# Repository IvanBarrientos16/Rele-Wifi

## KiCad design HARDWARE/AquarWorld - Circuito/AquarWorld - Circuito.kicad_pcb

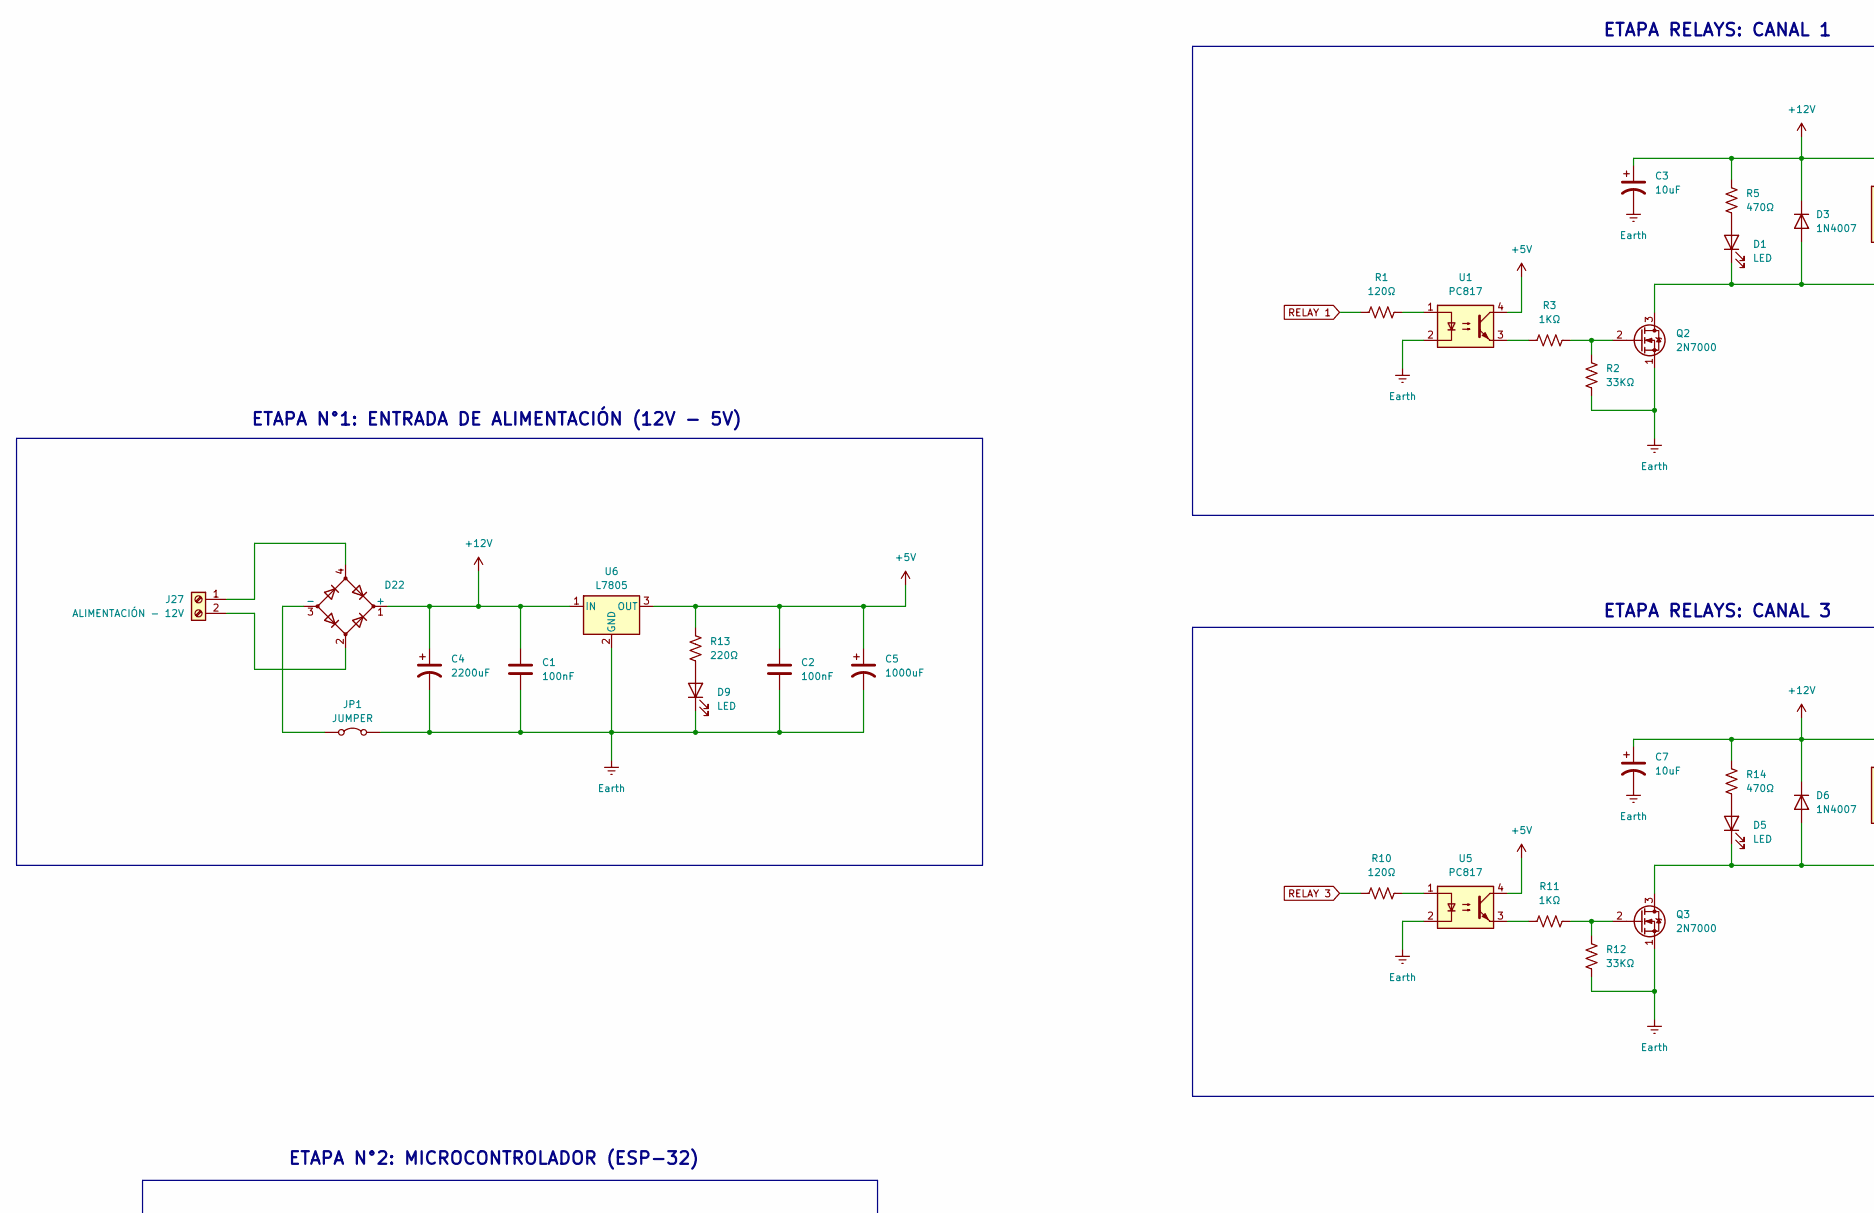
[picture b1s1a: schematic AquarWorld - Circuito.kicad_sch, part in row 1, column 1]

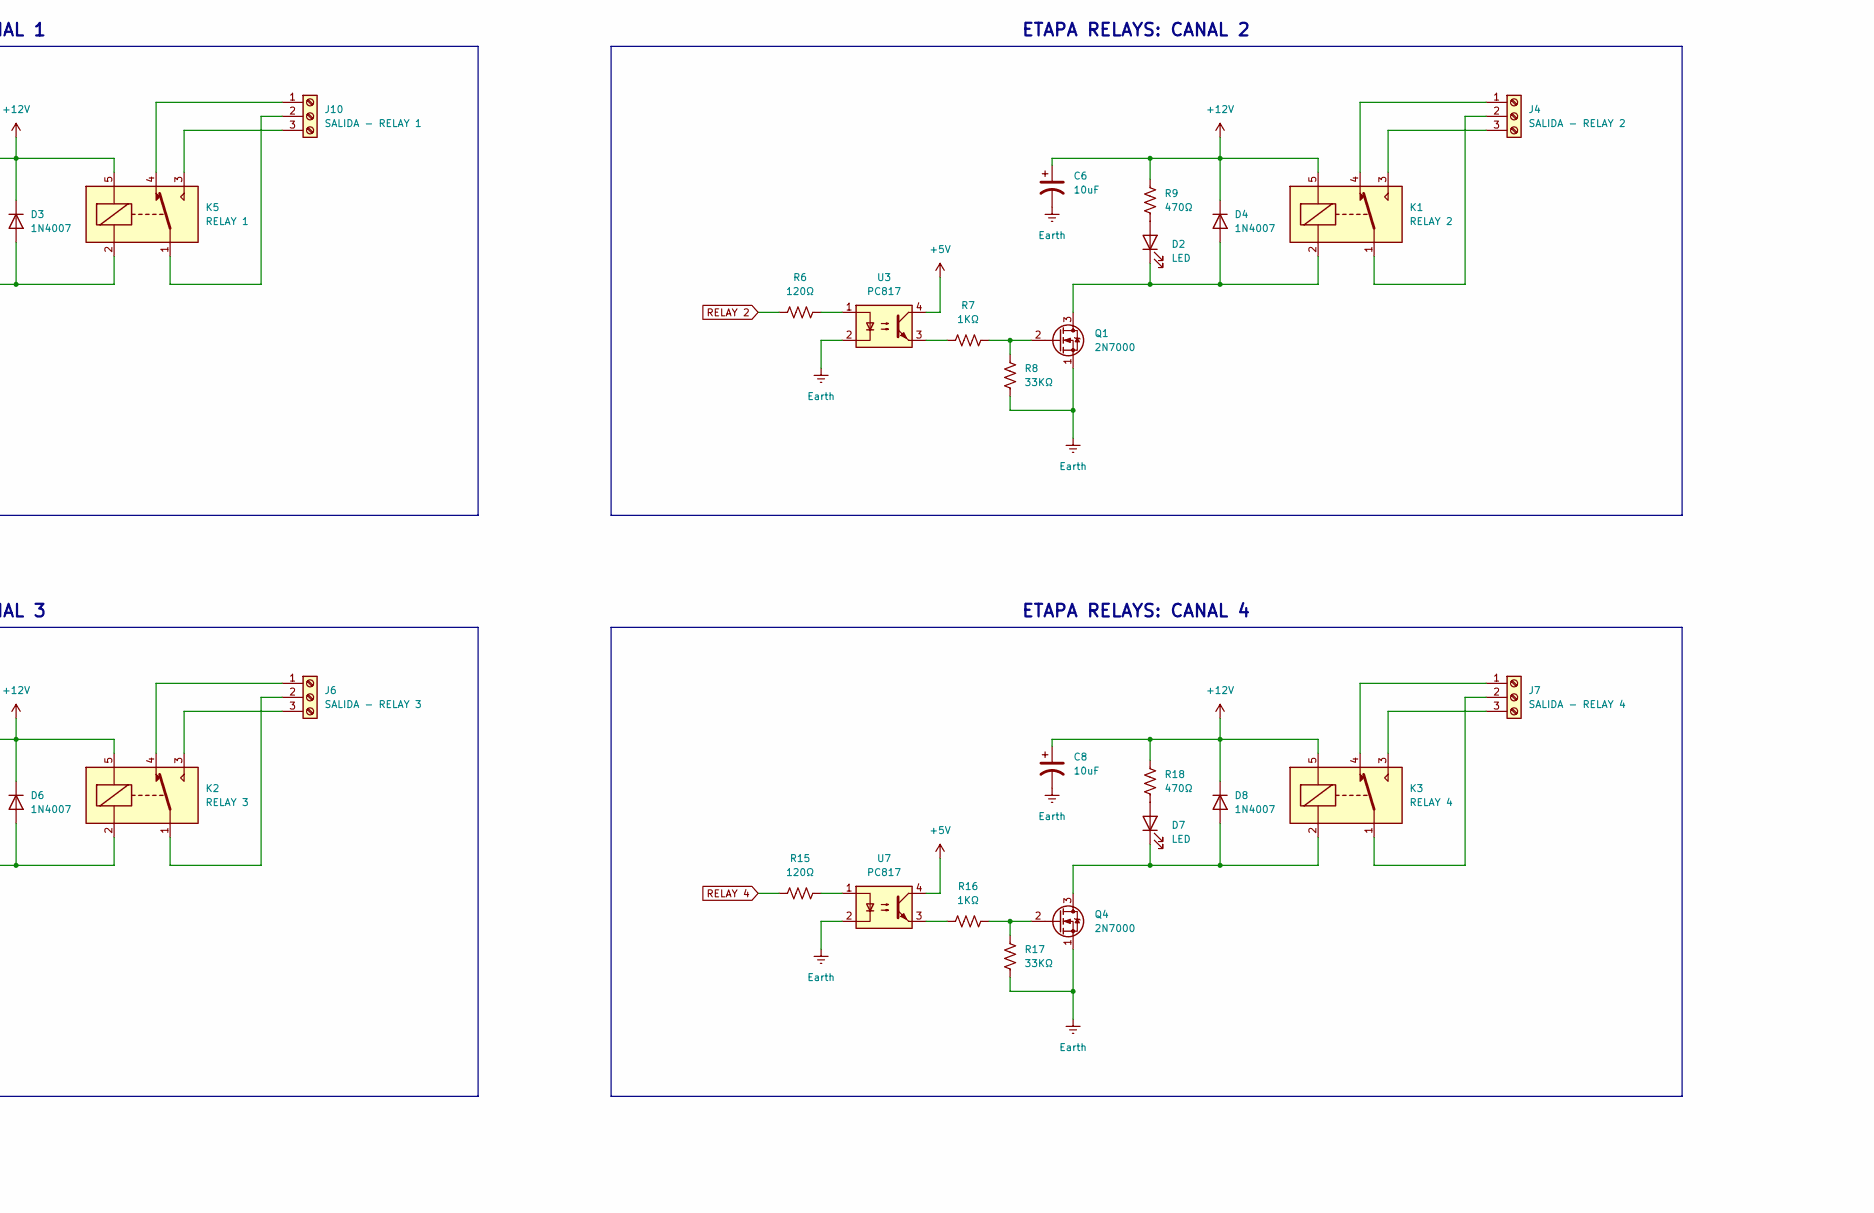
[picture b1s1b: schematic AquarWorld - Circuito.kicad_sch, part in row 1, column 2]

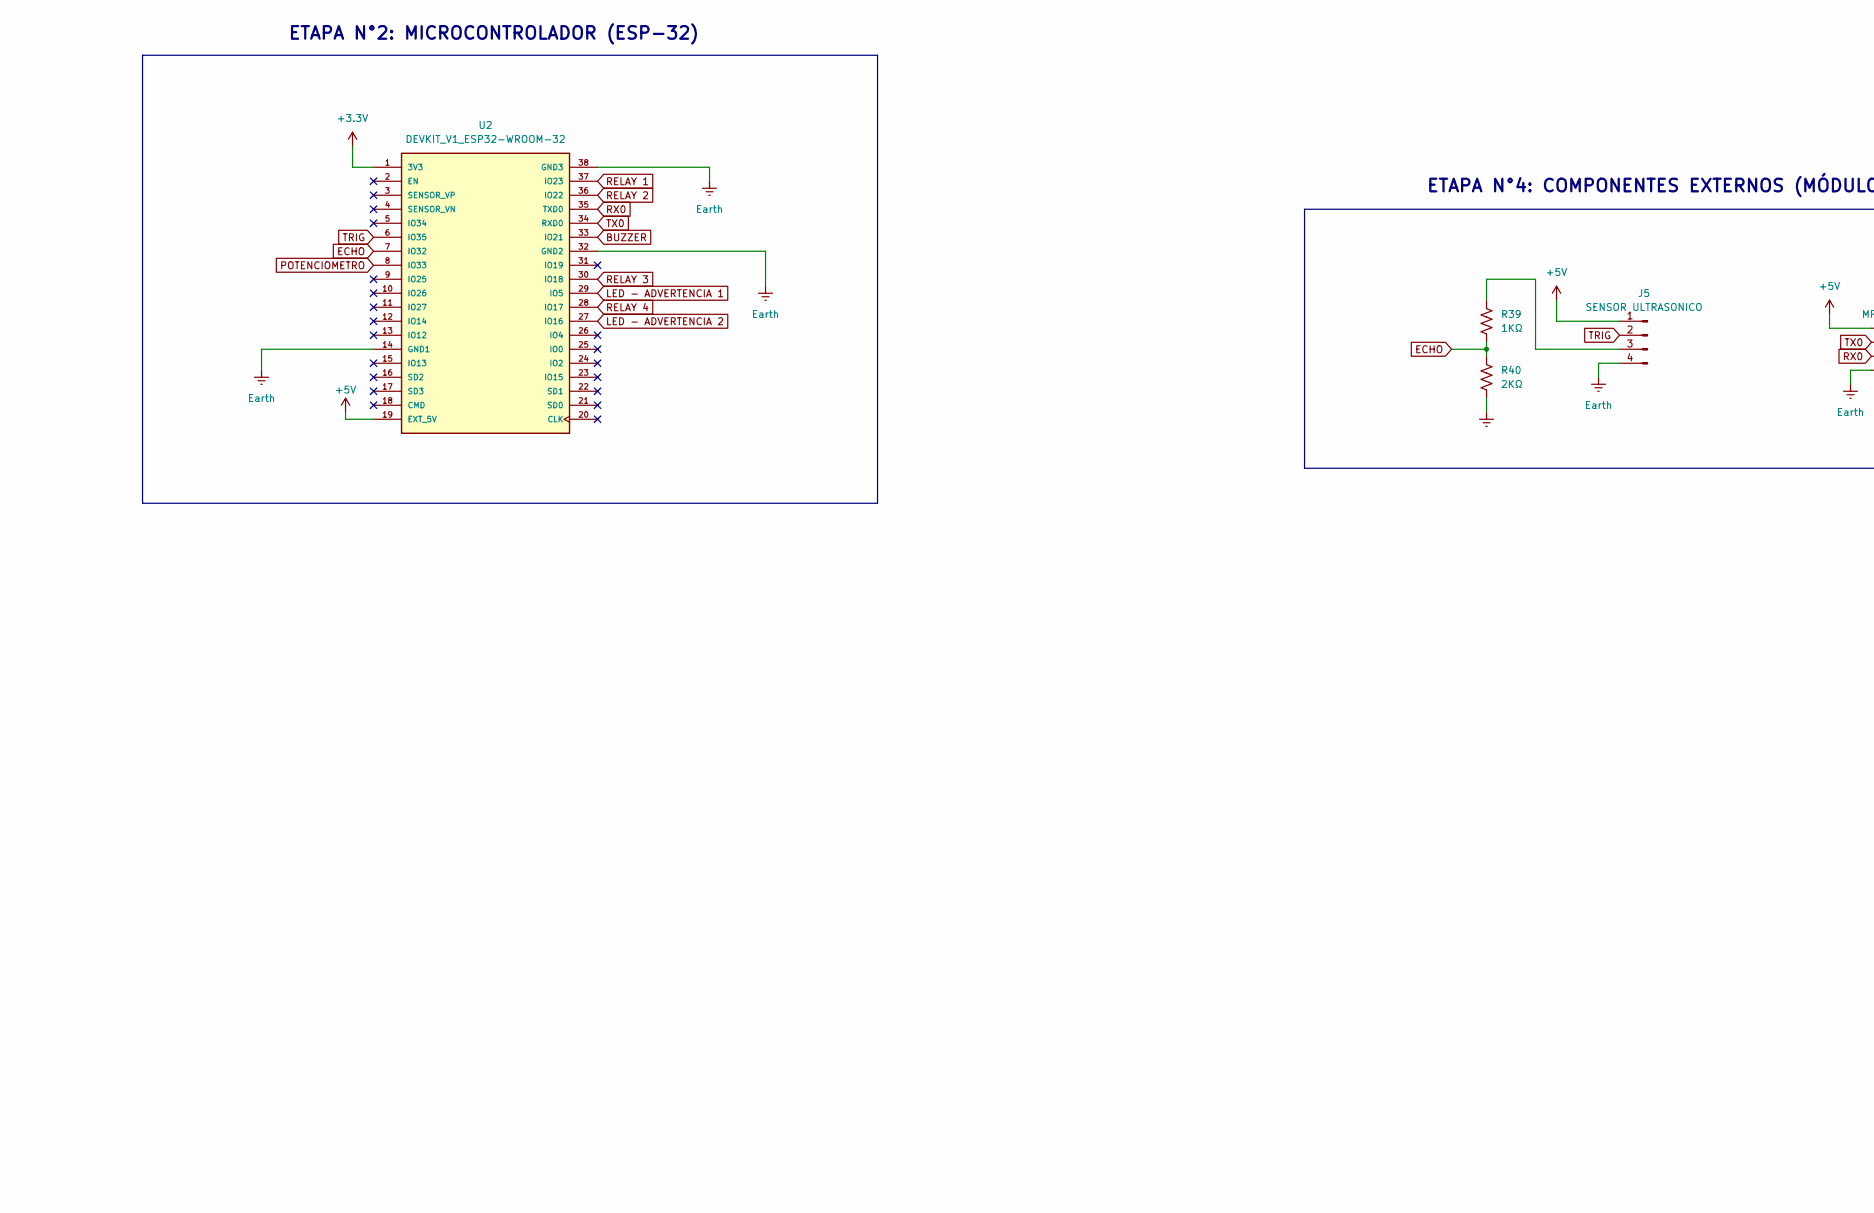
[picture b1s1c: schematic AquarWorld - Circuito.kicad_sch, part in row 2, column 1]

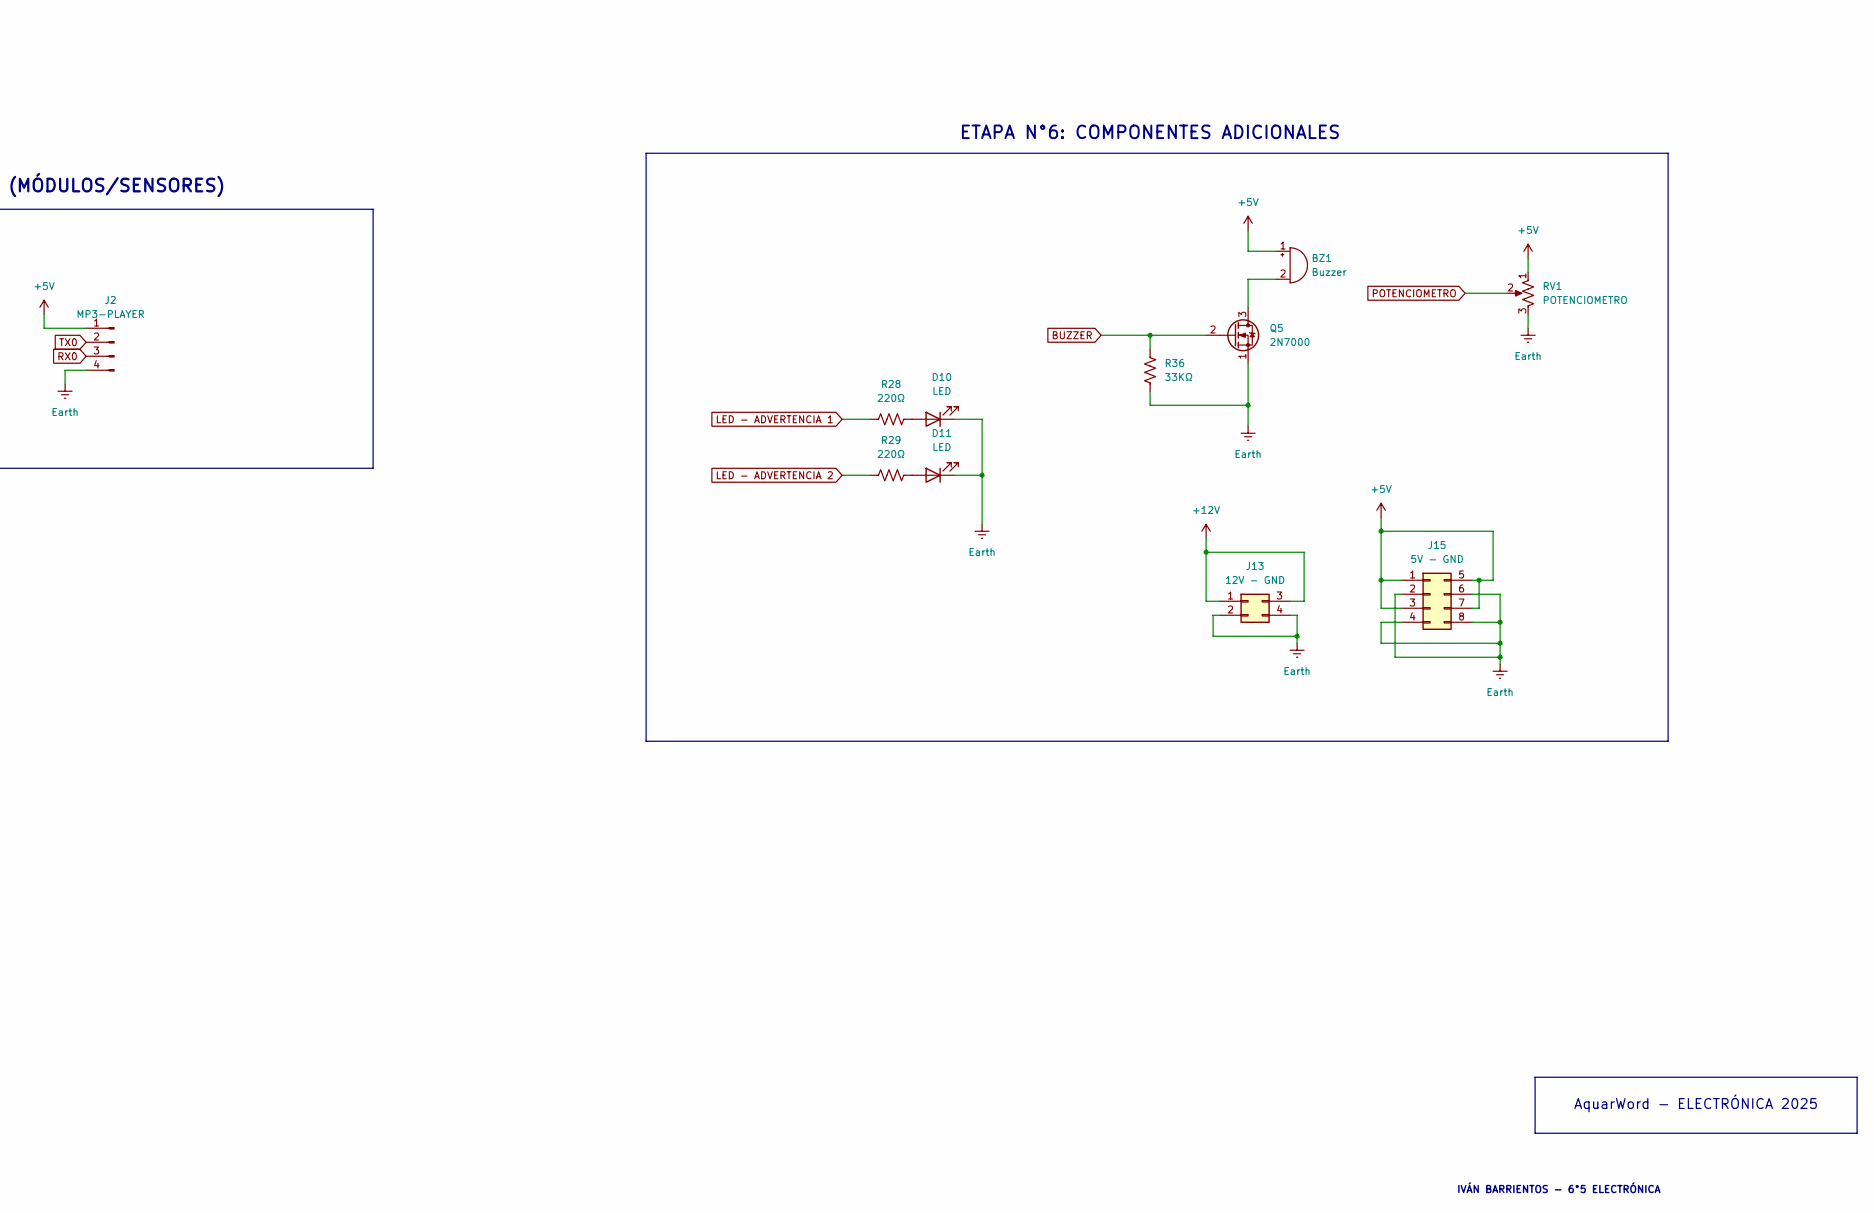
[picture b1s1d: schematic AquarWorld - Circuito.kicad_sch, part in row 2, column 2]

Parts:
BZ1: Buzzer; MagneticBuzzer_ProSignal_ABT-410-RC
C1, C2: 100nF; C_0805_2012Metric
C3, C6, C7, C8: 10uF; CP_Elec_6.3x5.4
C4: 2200uF; CP_Elec_10x10.5
C5: 1000uF; CP_Elec_8x10.5
D1, D2, D5, D7, D9: LED; LED_0805_2012Metric
D3, D4, D6, D8: 1N4007; D_SMA
D10, D11: LED; JST_XH_B2B-XH-A_1x02_P2.50mm_Vertical
D22: D_Bridge_+A-A; Diode_Bridge_Round_D9.8mm
J2: MP3-PLAYER; JST_XH_B4B-XH-A_1x04_P2.50mm_Vertical
J4: SALIDA - RELAY 2; TerminalBlock_bornier-3_P5.08mm
J5: SENSOR ULTRASONICO; JST_XH_B4B-XH-A_1x04_P2.50mm_Vertical
J6: SALIDA - RELAY 3; TerminalBlock_bornier-3_P5.08mm
J7: SALIDA - RELAY 4; TerminalBlock_bornier-3_P5.08mm
J10: SALIDA - RELAY 1; TerminalBlock_bornier-3_P5.08mm
J13: 12V - GND; PinHeader_2x02_P2.54mm_Vertical
J15: 5V - GND; PinHeader_2x04_P2.54mm_Vertical
J27: ALIMENTACIÓN - 12V; TerminalBlock_bornier-2_P5.08mm
JP1: JUMPER; PinHeader_1x02_P2.54mm_Vertical
K1: RELAY 2; Relay_SPDT_SANYOU_SRD_Series_Form_C
K2: RELAY 3; Relay_SPDT_SANYOU_SRD_Series_Form_C
K3: RELAY 4; Relay_SPDT_SANYOU_SRD_Series_Form_C
K5: RELAY 1; Relay_SPDT_SANYOU_SRD_Series_Form_C
Q1, Q2, Q3, Q4, Q5: 2N7000; SOT-23
R1, R6, R10, R15: 120Ω; R_0805_2012Metric
R2, R8, R12, R17: 33KΩ; R_0805_2012Metric
R3, R7, R11, R16: 1KΩ; R_0805_2012Metric
R5, R9, R14, R18: 470Ω; R_0805_2012Metric
R13: 220Ω; R_0805_2012Metric
R28, R29: 220Ω; R_0805_2012Metric
R36: 33KΩ; R_0805_2012Metric
R39: 1KΩ; R_0805_2012Metric
R40: 2KΩ; R_0805_2012Metric
RV1: POTENCIOMETRO; JST_XH_B3B-XH-A_1x03_P2.50mm_Vertical
U1, U3, U5, U7: PC817; SO-4_4.4x4.3mm_P2.54mm
U2: DEVKIT_V1_ESP32-WROOM-32; MODULE_DEVKIT_V1_ESP32-WROOM-32; PARTREV N/A
U6: L7805; TO-252-2

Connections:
+3.3V: U2.1 (3V3)
+5V: BZ1.1 (+), C2.1, C5.1, J2.1, J5.1, J15.1, J15.3, J15.5, J15.7, R13.1, RV1.1, U1.4, U2.19 (EXT_5V), U3.4, U5.4, U6.3 (OUT), U7.4
+12V: C1.1, C3.1, C4.1, C6.1, C7.1, C8.1, D3.1 (K), D4.1 (K), D6.1 (K), D8.1 (K), D22.1 (+), J13.1, J13.3, K1.5, K2.5, K3.5, K5.5, R5.1, R9.1, R14.1, R18.1, U6.1 (IN)
BUZZER: Q5.2 (G), R36.1, U2.33 (IO21)
ECHO: R39.2, R40.1, U2.7 (IO32)
Earth: C1.2, C2.2, C3.2, C4.2, C5.2, C6.2, C7.2, C8.2, D9.1 (K), D10.1 (K), D11.1 (K), J2.4, J5.4, J13.2, J13.4, J15.2, J15.4, J15.6, J15.8, JP1.2 (B), Q1.1 (S), Q2.1 (S), Q3.1 (S), Q4.1 (S), Q5.1 (S), R2.1, R8.1, R12.1, R17.1, R36.2, R40.2, RV1.3, U1.2, U2.14 (GND1), U2.32 (GND2), U2.38 (GND3), U3.2, U5.2, U6.2 (GND), U7.2
LED - ADVERTENCIA 1: R28.2, U2.29 (IO5)
LED - ADVERTENCIA 2: R29.2, U2.27 (IO16)
unnamed: BZ1.2 (-), Q5.3 (D)
unnamed: D1.2 (A), R5.2
unnamed: D1.1 (K), D3.2 (A), K5.2, Q2.3 (D)
unnamed: D2.2 (A), R9.2
unnamed: D2.1 (K), D4.2 (A), K1.2, Q1.3 (D)
unnamed: D5.2 (A), R14.2
unnamed: D5.1 (K), D6.2 (A), K2.2, Q3.3 (D)
unnamed: D7.2 (A), R18.2
unnamed: D7.1 (K), D8.2 (A), K3.2, Q4.3 (D)
unnamed: D9.2 (A), R13.2
unnamed: D10.2 (A), R28.1
unnamed: D11.2 (A), R29.1
unnamed: D22.3 (-), JP1.1 (A)
unnamed: J4.1, K1.4
unnamed: J4.2, K1.1
unnamed: J4.3, K1.3
unnamed: J5.3, R39.1
unnamed: J6.1, K2.4
unnamed: J6.2, K2.1
unnamed: J6.3, K2.3
unnamed: J7.1, K3.4
unnamed: J7.2, K3.1
unnamed: J7.3, K3.3
unnamed: J10.1, K5.4
unnamed: J10.2, K5.1
unnamed: J10.3, K5.3
unnamed: D22.4, J27.1
unnamed: D22.2, J27.2
unnamed: Q1.2 (G), R7.1, R8.2
unnamed: Q2.2 (G), R2.2, R3.1
unnamed: Q3.2 (G), R11.1, R12.2
unnamed: Q4.2 (G), R16.1, R17.2
unnamed: R1.1, U1.1
unnamed: R3.2, U1.3
unnamed: R6.1, U3.1
unnamed: R7.2, U3.3
unnamed: R10.1, U5.1
unnamed: R11.2, U5.3
unnamed: R15.1, U7.1
unnamed: R16.2, U7.3
POTENCIOMETRO: RV1.2, U2.8 (IO33)
RELAY 1: R1.2, U2.37 (IO23)
RELAY 2: R6.2, U2.36 (IO22)
RELAY 3: R10.2, U2.30 (IO18)
RELAY 4: R15.2, U2.28 (IO17)
RX0: J2.3, U2.35 (TXD0)
TRIG: J5.2, U2.6 (IO35)
TX0: J2.2, U2.34 (RXD0)

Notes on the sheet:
ETAPA RELAYS: CANAL 3
ETAPA RELAYS: CANAL 2
ETAPA N°1: ENTRADA DE ALIMENTACIÓN (12V - 5V)
AquarWord - ELECTRÓNICA 2025
ETAPA RELAYS: CANAL 1
ETAPA RELAYS: CANAL 4
IVÁN BARRIENTOS - 6°5 ELECTRÓNICA
ETAPA N°2: MICROCONTROLADOR (ESP-32)
ETAPA N°4: COMPONENTES EXTERNOS (MÓDULOS/SENSORES)
ETAPA N°6: COMPONENTES ADICIONALES

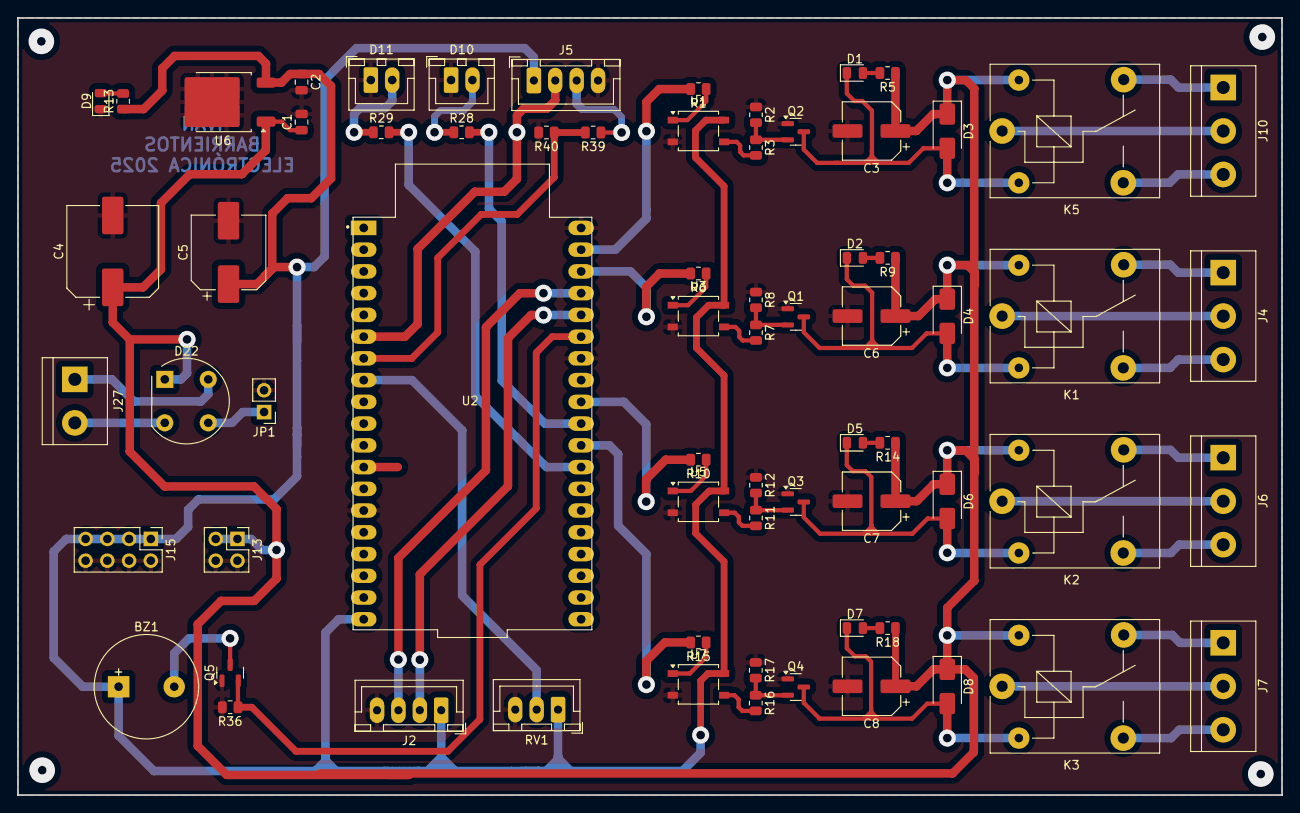
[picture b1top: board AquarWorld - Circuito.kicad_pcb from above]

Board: 2 copper layers, 147.7 x 90.8 mm, 69 parts (0 on the bottom side), 55 nets.

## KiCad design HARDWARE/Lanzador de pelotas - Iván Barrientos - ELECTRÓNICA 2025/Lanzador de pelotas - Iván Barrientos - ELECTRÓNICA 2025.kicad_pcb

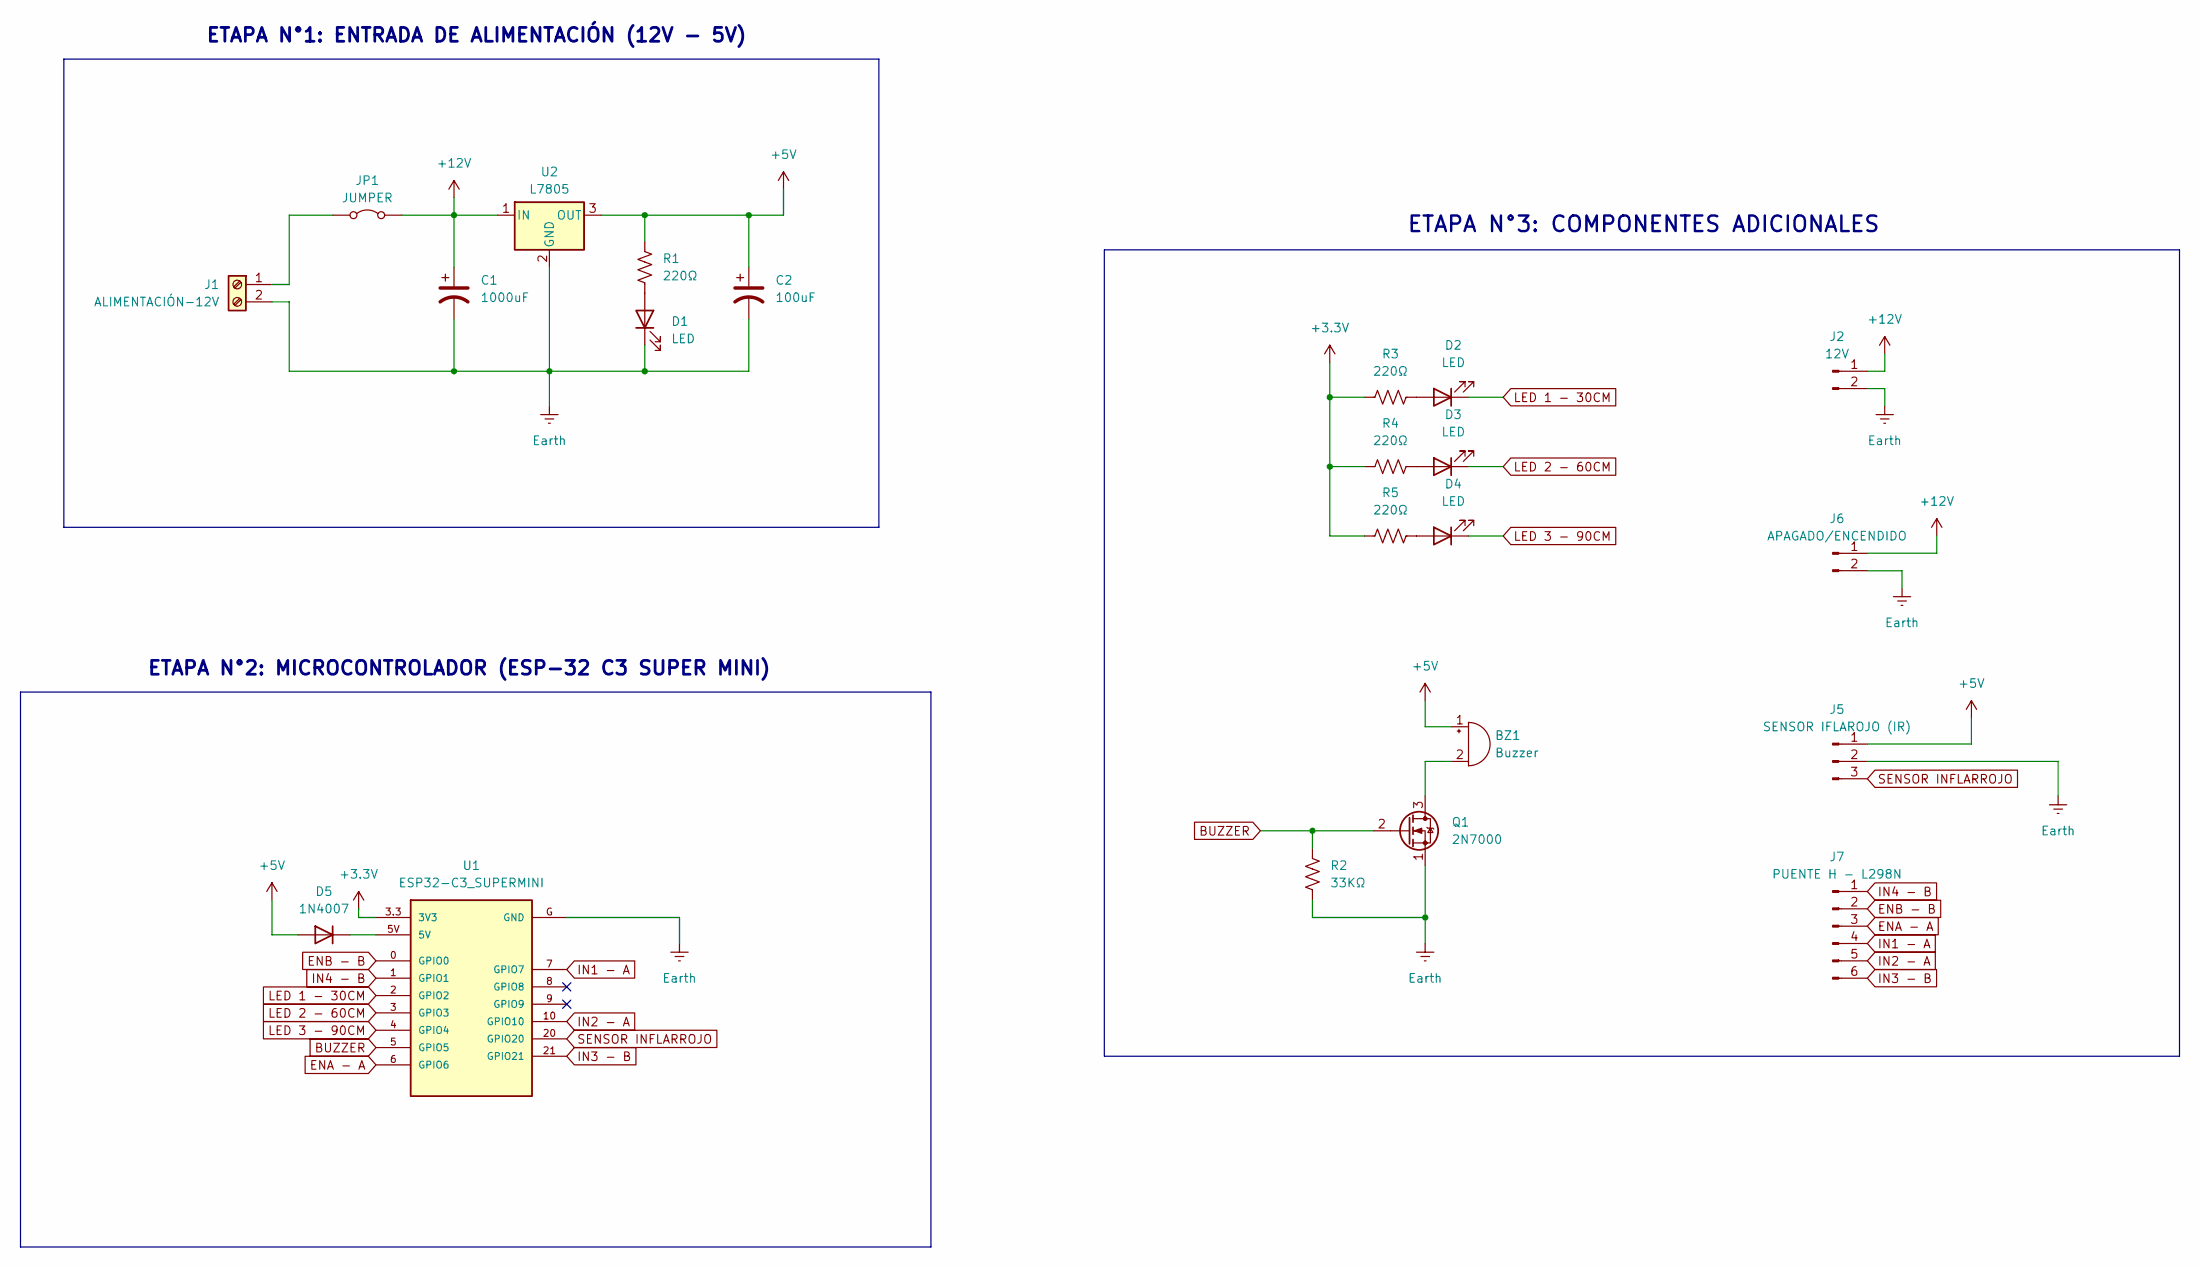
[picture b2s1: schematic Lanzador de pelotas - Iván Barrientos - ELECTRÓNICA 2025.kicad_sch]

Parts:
BZ1: Buzzer; MagneticBuzzer_ProSignal_ABT-410-RC
C1: 1000uF; CP_Elec_8x10.5
C2: 100uF; CP_Elec_6.3x5.8
D1: LED; LED_0805_2012Metric
D2, D3, D4: LED; JST_XH_B2B-XH-A_1x02_P2.50mm_Vertical
D5: 1N4007; D_0805_2012Metric
J1: ALIMENTACIÓN-12V; TerminalBlock_bornier-2_P5.08mm
J2: 12V; PinHeader_1x02_P2.54mm_Vertical
J5: SENSOR IFLAROJO (IR); JST_XH_B3B-XH-A_1x03_P2.50mm_Vertical
J6: APAGADO/ENCENDIDO; JST_XH_B2B-XH-A_1x02_P2.50mm_Vertical
J7: PUENTE H - L298N; JST_XH_B6B-XH-A_1x06_P2.50mm_Vertical
JP1: JUMPER; PinHeader_1x02_P2.54mm_Vertical
Q1: 2N7000; SOT-23
R1: 220Ω; R_0805_2012Metric
R2: 33KΩ; R_0805_2012Metric
R3, R4, R5: 220Ω; R_0805_2012Metric
U1: ESP32-C3_SUPERMINI; MODULE_ESP32-C3_SUPERMINI
U2: L7805; TO-252-2

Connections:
+3.3V: R3.2, R4.2, R5.2, U1.3.3 (3V3)
+5V: BZ1.1 (+), C2.1, D5.2 (A), J5.1, R1.1, U2.3 (OUT)
+12V: C1.1, J2.1, J6.1, JP1.2 (B), U2.1 (IN)
BUZZER: Q1.2 (G), R2.1, U1.5 (GPIO5)
ENA - A: J7.3, U1.6 (GPIO6)
ENB - B: J7.2, U1.0 (GPIO0)
Earth: C1.2, C2.2, D1.1 (K), J1.2, J2.2, J5.2, J6.2, Q1.1 (S), R2.2, U1.G (GND), U2.2 (GND)
IN1 - A: J7.4, U1.7 (GPIO7)
IN2 - A: J7.5, U1.10 (GPIO10)
IN3 - B: J7.6, U1.21 (GPIO21)
IN4 - B: J7.1, U1.1 (GPIO1)
LED 1 - 30CM: D2.1 (K), U1.2 (GPIO2)
LED 2 - 60CM: D3.1 (K), U1.3 (GPIO3)
LED 3 - 90CM: D4.1 (K), U1.4 (GPIO4)
unnamed: BZ1.2 (-), Q1.3 (D)
unnamed: D1.2 (A), R1.2
unnamed: D2.2 (A), R3.1
unnamed: D3.2 (A), R4.1
unnamed: D4.2 (A), R5.1
unnamed: D5.1 (K), U1.5V
unnamed: J1.1, JP1.1 (A)
SENSOR INFLARROJO: J5.3, U1.20 (GPIO20)

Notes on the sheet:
ETAPA N°1: ENTRADA DE ALIMENTACIÓN (12V - 5V)
ETAPA N°3: COMPONENTES ADICIONALES
ETAPA N°2: MICROCONTROLADOR (ESP-32 C3 SUPER MINI)

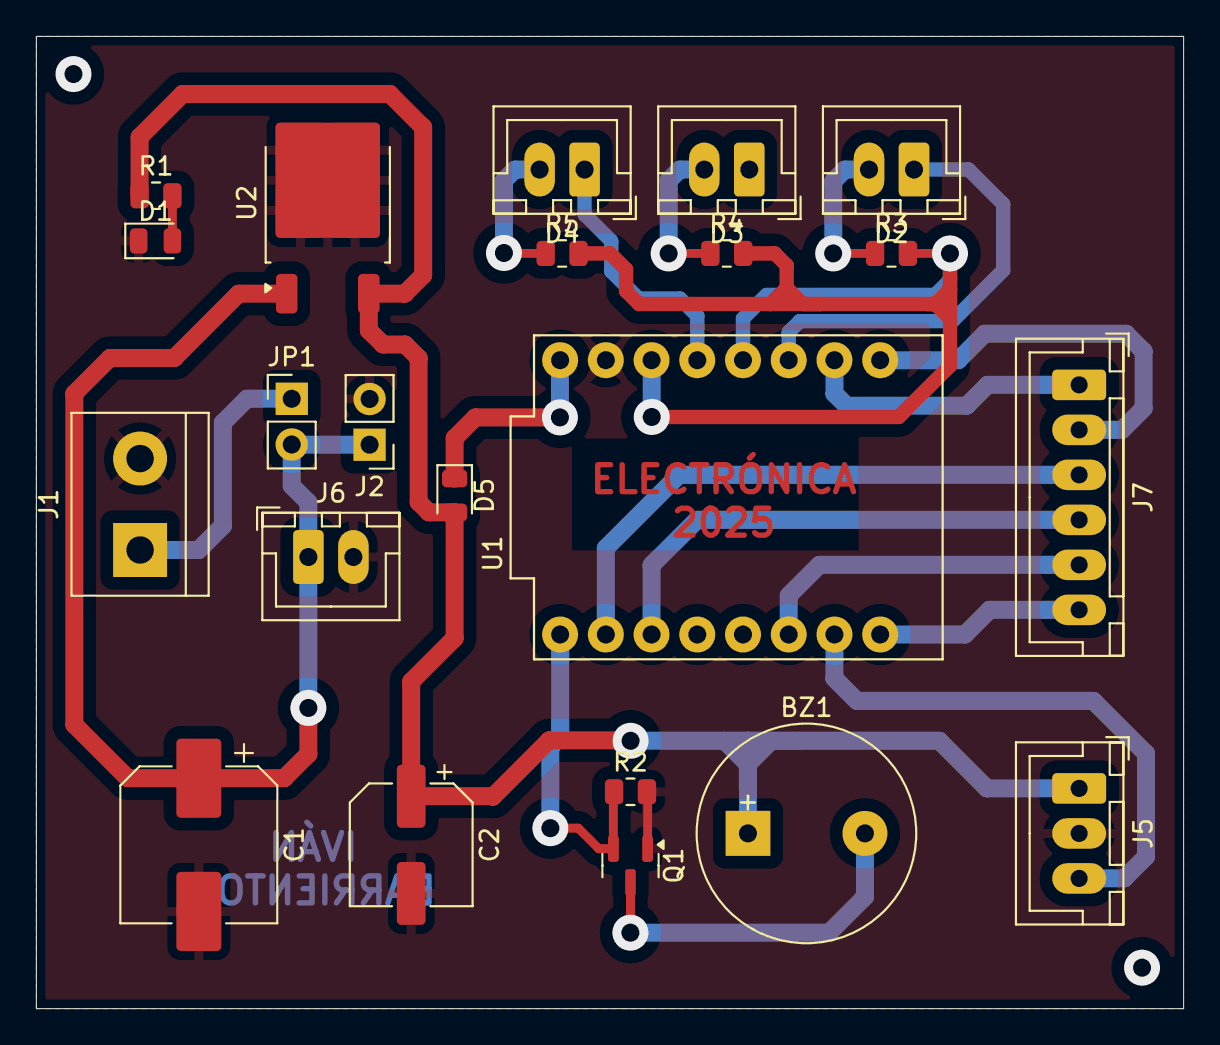
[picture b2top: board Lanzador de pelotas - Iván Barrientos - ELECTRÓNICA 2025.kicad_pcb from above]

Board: 2 copper layers, 63.7 x 54.0 mm, 22 parts (0 on the bottom side), 22 nets.

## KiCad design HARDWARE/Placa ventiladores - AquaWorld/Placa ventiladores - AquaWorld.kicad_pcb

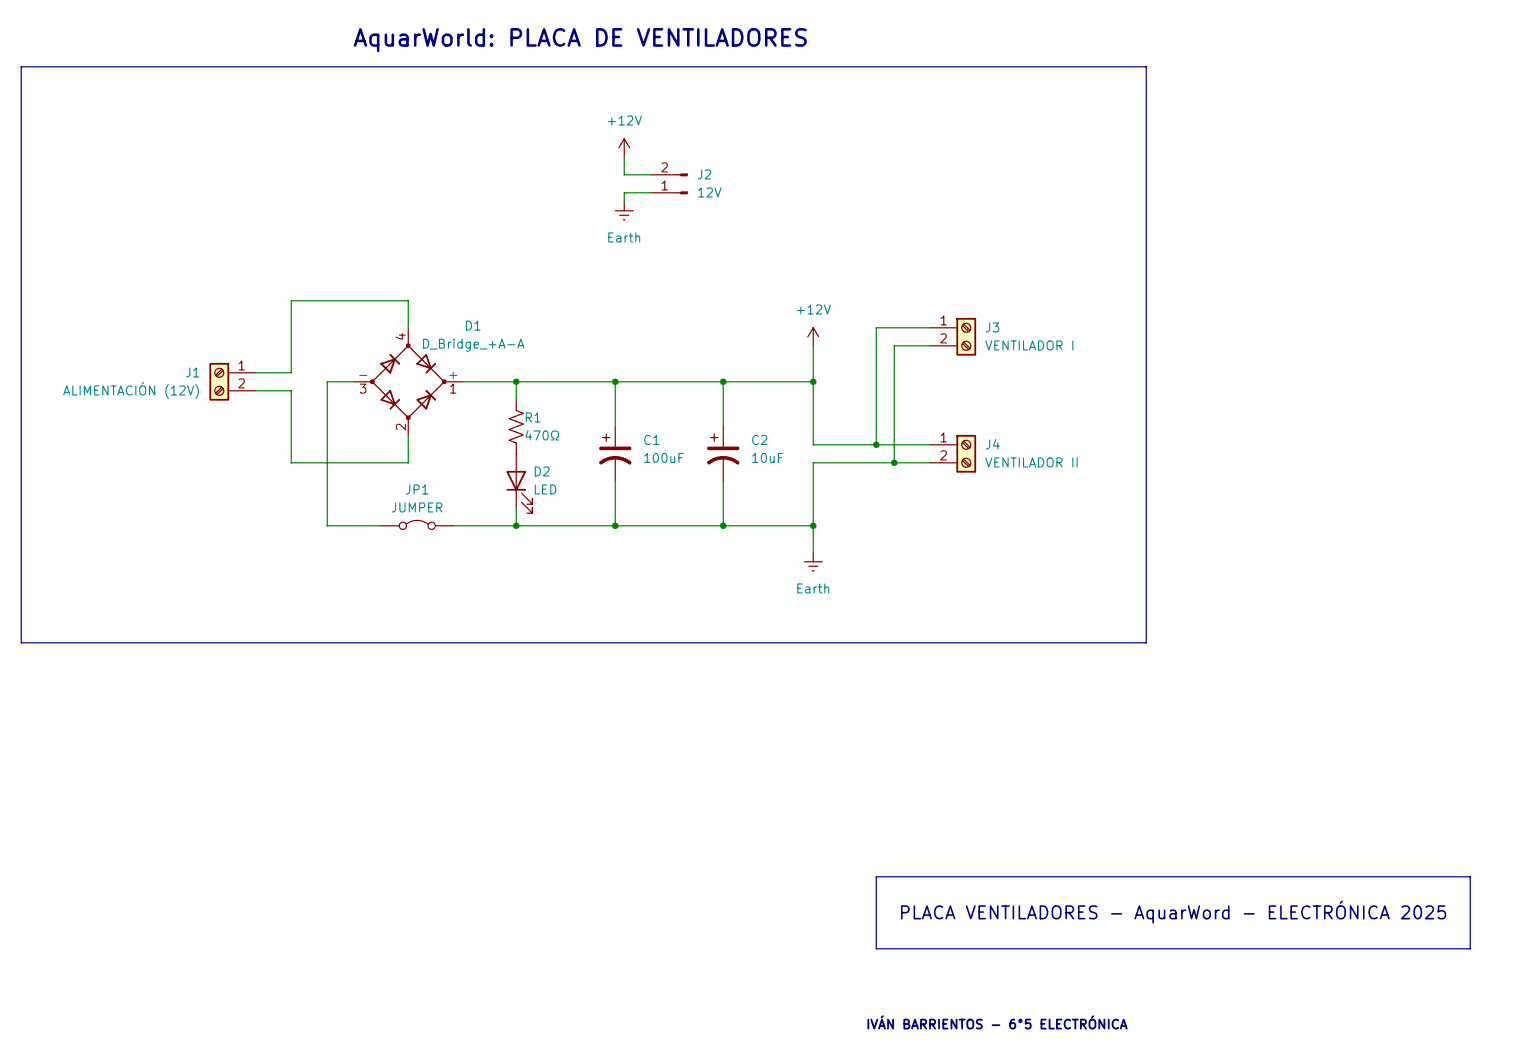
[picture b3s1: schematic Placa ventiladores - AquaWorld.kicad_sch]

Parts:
C1: 100uF; CP_Elec_6.3x5.8
C2: 10uF; CP_Elec_6.3x5.4
D1: D_Bridge_+A-A; Diode_Bridge_Round_D9.8mm
D2: LED; LED_0805_2012Metric
J1: ALIMENTACIÓN (12V); TerminalBlock_bornier-2_P5.08mm
J2: 12V; PinHeader_1x02_P2.54mm_Vertical
J3: VENTILADOR I; JST_XH_B2B-XH-A_1x02_P2.50mm_Vertical
J4: VENTILADOR II; JST_XH_B2B-XH-A_1x02_P2.50mm_Vertical
JP1: JUMPER; PinHeader_1x02_P2.54mm_Vertical
R1: 470Ω; R_0805_2012Metric

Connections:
+12V: C1.1, C2.1, D1.1 (+), J2.2, J3.1, J4.1, R1.1
Earth: C1.2, C2.2, D2.1 (K), J2.1, J3.2, J4.2, JP1.2 (B)
unnamed: D1.3 (-), JP1.1 (A)
unnamed: D2.2 (A), R1.2
unnamed: D1.4, J1.1
unnamed: D1.2, J1.2

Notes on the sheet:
IVÁN BARRIENTOS - 6°5 ELECTRÓNICA
PLACA VENTILADORES - AquarWord - ELECTRÓNICA 2025
AquarWorld: PLACA DE VENTILADORES

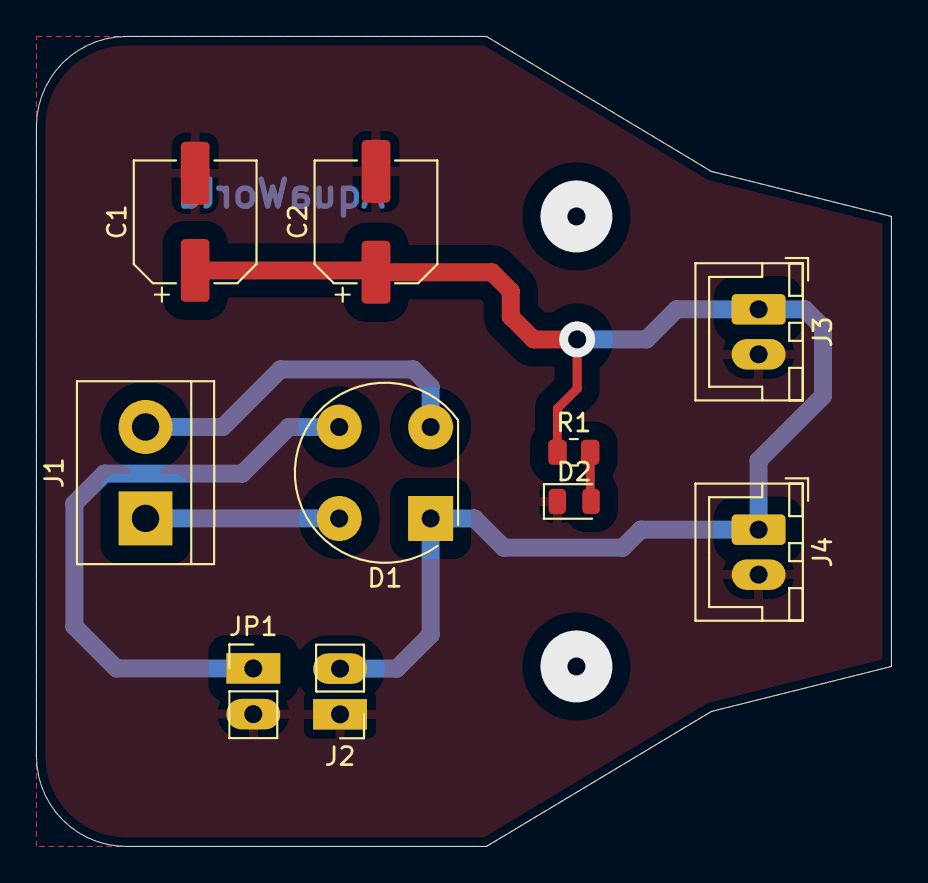
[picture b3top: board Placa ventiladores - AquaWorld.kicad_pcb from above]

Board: 2 copper layers, 47.5 x 45.0 mm, 10 parts (0 on the bottom side), 6 nets.

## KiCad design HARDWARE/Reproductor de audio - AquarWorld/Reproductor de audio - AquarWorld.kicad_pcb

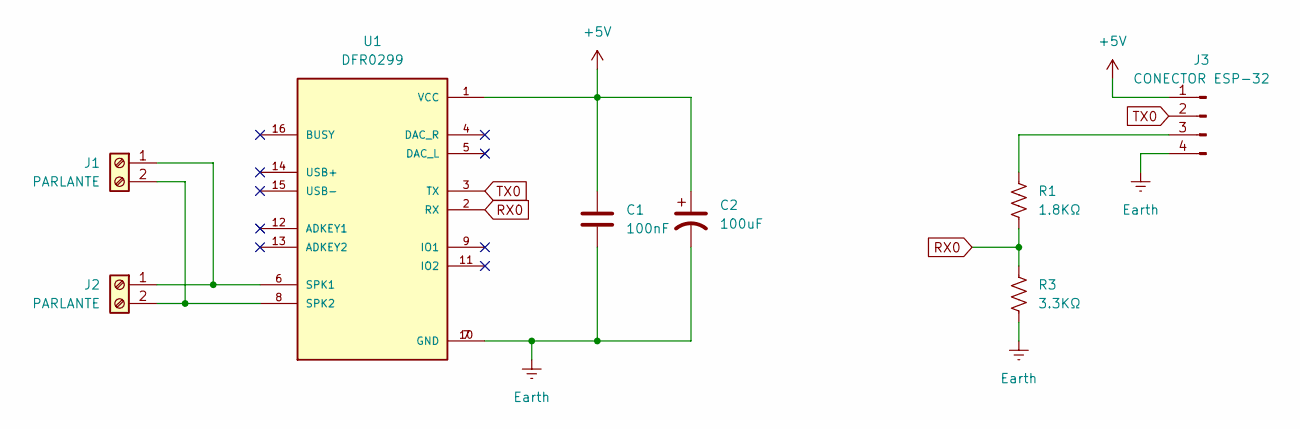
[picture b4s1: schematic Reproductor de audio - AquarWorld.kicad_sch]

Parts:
C1: 100nF; C_0805_2012Metric
C2: 100uF; CP_Elec_8x10.5
J1, J2: PARLANTE; JST_XH_B2B-XH-A_1x02_P2.50mm_Vertical
J3: CONECTOR ESP-32; JST_XH_B4B-XH-A_1x04_P2.50mm_Vertical
R1: 1.8KΩ; R_0805_2012Metric
R3: 3.3KΩ; R_0805_2012Metric
U1: DFR0299; MODULE_DFR0299; DigiKey_Part_Number 1738-1041-ND

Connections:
+5V: C1.1, C2.1, J3.1, U1.1 (VCC)
Earth: C1.2, C2.2, J3.4, R3.1, U1.7 (GND), U1.10 (GND)
unnamed: J1.1, J2.1, U1.6 (SPK1)
unnamed: J1.2, J2.2, U1.8 (SPK2)
unnamed: J3.3, R1.2
RX0: R1.1, R3.2, U1.2 (RX)
TX0: J3.2, U1.3 (TX)

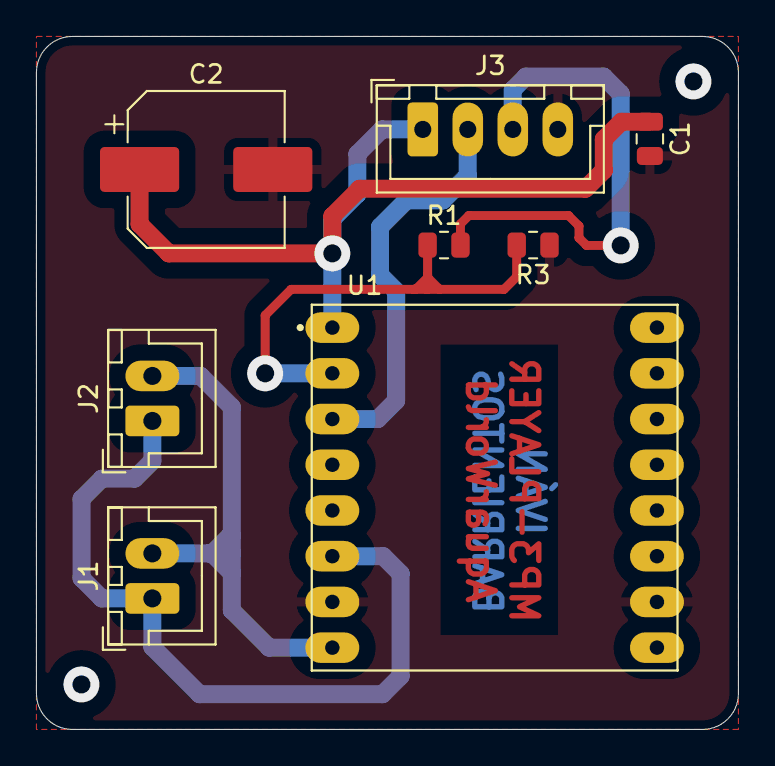
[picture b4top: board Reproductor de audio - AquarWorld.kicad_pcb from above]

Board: 2 copper layers, 39.0 x 38.5 mm, 8 parts (0 on the bottom side), 7 nets.

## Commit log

2025-05-13 Subiendo proyecto con carpetas 3D, Hardware y Software
2025-05-13 Agregué carpeta 'AquarWorld - Circuito' en HARDWARE
2025-05-30 Agregué esquemático de la placa de ventiladores a la carpeta Hardware
2025-06-05 Eliminé la carpeta 'AquarWorld - Circuito' de HARDWARE
2025-06-05 Eliminé la carpeta 'Placa ventiladores - AquaWorld' de HARDWARE
2025-06-05 Agregué la placa de los ventiladores a la carpeta Hardware
2025-06-08 Placa reproductor de audio MP3-Player
2025-06-08 Eliminé la carpeta 'Placa ventiladores' de HARDWARE
2025-06-08 Placa de ventiladores - AquarWorld
2025-06-08 Eliminé la carpeta 'Reproductor de audio' de HARDWARE
2025-06-08 Placa reproductora de audio MP3-Player
2025-06-17 Eliminé la carpeta 'Placa ventiladores - AquarWorld' de HARDWARE
2025-06-17 Placas finales - AquarWorld
2025-06-17 Placa pricipal - AquarWorld
2025-06-18 Placas corregidas
2025-06-18 Lanzador de pelotas - Iván Barrientos
2025-06-18 Lanzador de pelotas
2025-06-18 Placa principal - AquarWorld
